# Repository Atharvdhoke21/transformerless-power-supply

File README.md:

# Transformerless Power Supply

## Overview

This project is a compact transformerless AC to DC power supply designed using the capacitive dropper technique. The circuit converts 230V AC mains supply into regulated low-voltage DC output suitable for low-power embedded systems and electronic applications.

## Features

- Compact PCB design
- Low-cost implementation
- 230V AC input
- Regulated DC output
- Designed using KiCad
- Capacitive dropper topology

## Working Principle

The circuit uses a capacitor dropper method to reduce AC mains voltage without using a bulky transformer.

Main stages:
1. Capacitor dropper
2. Rectification
3. Filtering
4. Voltage regulation

The AC current is limited using an X-rated capacitor. The reduced AC voltage is rectified using a bridge rectifier and filtered using electrolytic capacitors. A Zener diode is used for voltage regulation.

## Circuit Formula

Capacitive reactance:

Xc = 1 / (2πfC)

This reactance limits the current flowing through the circuit.

## Components Used

- Zener diode
- Electrolytic capacitor
- Resistors
- LED indicator

## Software Used

- KiCad

## PCB Layout

## Schematic

## 3D PCB View

## Applications

- Low-power embedded systems
- Sensor circuits
- IoT modules
- Home automation devices

## Safety Warning

⚠ WARNING:
This project directly interfaces with AC mains voltage and does not provide isolation from the mains supply.

Improper handling may cause severe electric shock.

Use proper safety precautions while testing and operating the circuit.

## Author

Atharv Dhoke

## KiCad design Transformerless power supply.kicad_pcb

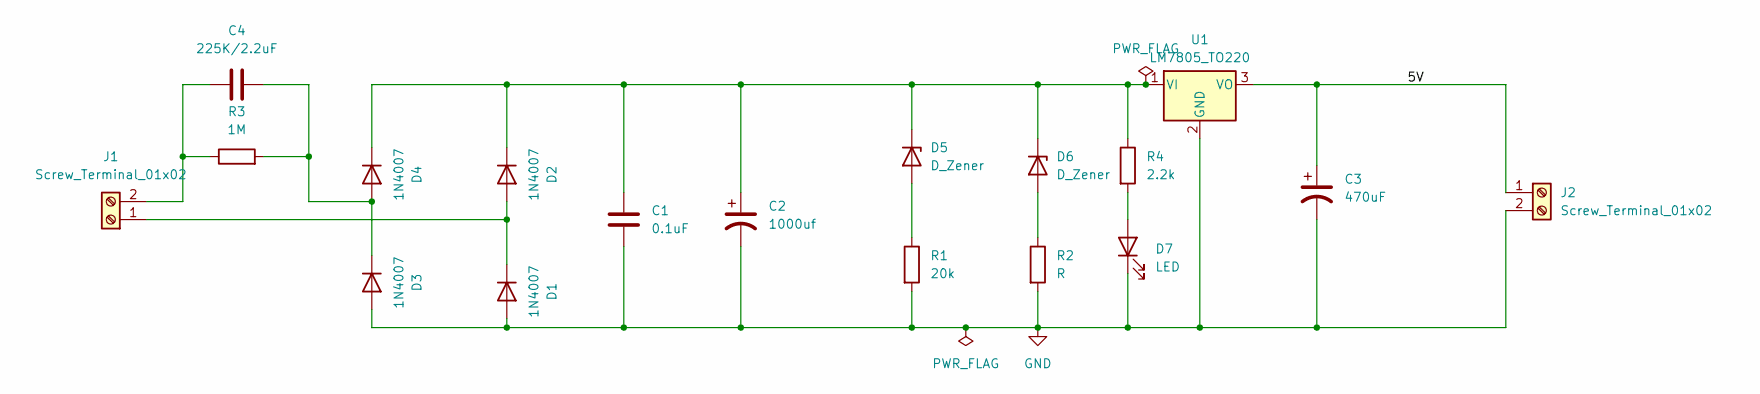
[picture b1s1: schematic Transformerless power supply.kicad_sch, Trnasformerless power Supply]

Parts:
C1: 0.1uF; C_Disc_D4.7mm_W2.5mm_P5.00mm
C2: 1000uf; CP_Radial_D8.0mm_P5.00mm
C3: 470uF; CP_Radial_D10.0mm_P3.80mm
C4: 225K/2.2uF; C_Rect_L18.0mm_W6.0mm_P15.00mm_FKS3_FKP3
D1, D2, D3, D4: 1N4007; D_DO-41_SOD81_P10.16mm_Horizontal
D5, D6: D_Zener; D_A-405_P7.62mm_Horizontal
D7: LED; LED_D5.0mm
J1, J2: Screw_Terminal_01x02; TerminalBlock_bornier-2_P5.08mm
R1: 20k; R_Axial_DIN0204_L3.6mm_D1.6mm_P7.62mm_Horizontal
R2: R; R_Axial_DIN0207_L6.3mm_D2.5mm_P7.62mm_Horizontal
R3: 1M; R_Axial_DIN0207_L6.3mm_D2.5mm_P7.62mm_Horizontal
R4: 2.2k
U1: LM7805_TO220; TO-220-3_Vertical

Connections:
/5V: C3.1, J2.1, U1.3 (VO)
GND: C1.2, C2.2, C3.2, D1.2 (A), D3.2 (A), D7.1 (K), J2.2, R1.2, R2.2, U1.2 (GND)
unnamed: D1.1 (K), D2.2 (A), J1.1
unnamed: C1.1, C2.1, D2.1 (K), D4.1 (K), D5.1 (K), D6.1 (K), R4.1, U1.1 (VI)
unnamed: C4.1, D3.1 (K), D4.2 (A), R3.2
unnamed: D5.2 (A), R1.1
unnamed: D6.2 (A), R2.1
unnamed: D7.2 (A), R4.2
unnamed: C4.2, J1.2, R3.1

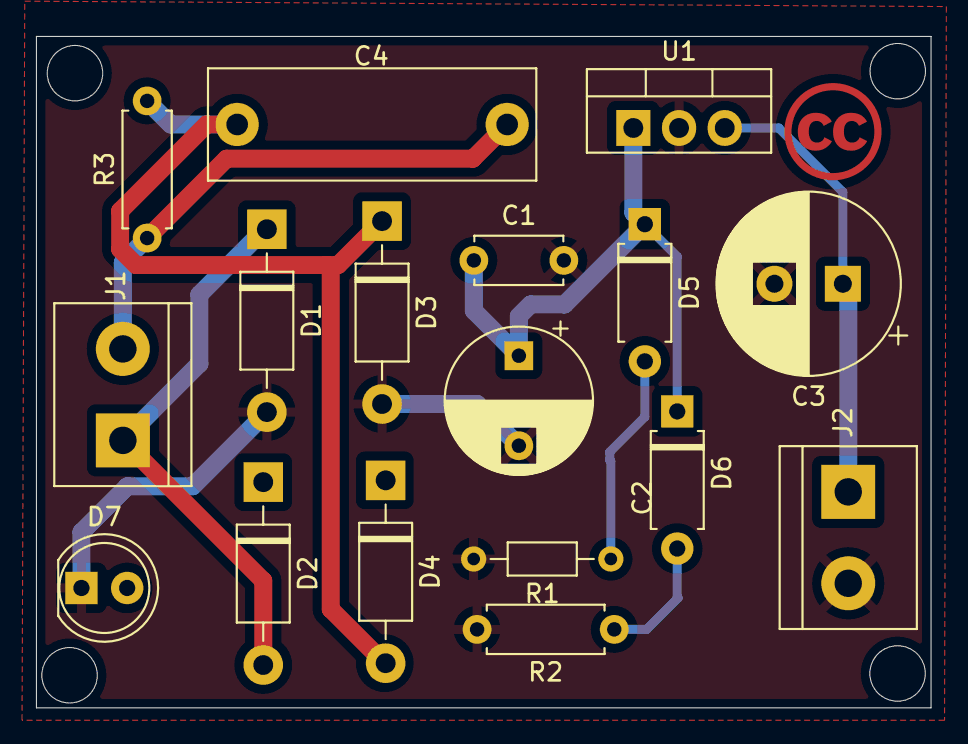
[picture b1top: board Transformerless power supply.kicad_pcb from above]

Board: 2 copper layers, 49.7 x 37.3 mm, 17 parts (0 on the bottom side), 8 nets.

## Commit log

2026-05-11 Enhance README with project details and warnings
    Added detailed project description and features.
2026-05-11 Create images
2026-05-11 Create temp
